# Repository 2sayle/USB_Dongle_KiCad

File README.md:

# USB Dongle (KiCad project)

KiCad project to create a custom USB-C key with mass storage and a microSD connector.
Find all the KiCad schematics and layout files.
Libraries containing custom footprints and symbols are available in ./Libraries folder.

## Hardware

- USB-C connector
- USB 2.0 High Speed Interface (through ULPI)
- STM32F730R8T microcontroller
- MicroSD connector
- Power LEDs
- GPIOs for SWD (Serial Wire Debug)

## Requirements

List any software requirements or dependencies needed to use or modify the project. For a KiCad project, this would include:

- KiCad EDA Suite version 7.0.2

## Installation

```
git clone https://github.com/2sayle/USB_Dongle_KiCad.git
```

## Usage

Explain how to use the project, with examples and screenshots if applicable.

## Documentation

Links to additional documentation for the project, such as a user manual or technical specifications.
- [STM32F730 Reference Manual](https://www.st.com/resource/en/reference_manual/rm0431-stm32f72xxx-and-stm32f73xxx-advanced-armbased-32bit-mcus-stmicroelectronics.pdf)
- [STM32F730R8 Datasheet](https://www.st.com/resource/en/datasheet/stm32f730i8.pdf)
- [ULPI Interface](http://ww1.microchip.com/downloads/en/DeviceDoc/334x.pdf)
- [USB ESD Protection](https://www.st.com/resource/en/datasheet/usbulc6-2m6.pdf)

Note: Datasheets are also available by selecting a component and pressing 'D' key, in KiCad schematics editor.

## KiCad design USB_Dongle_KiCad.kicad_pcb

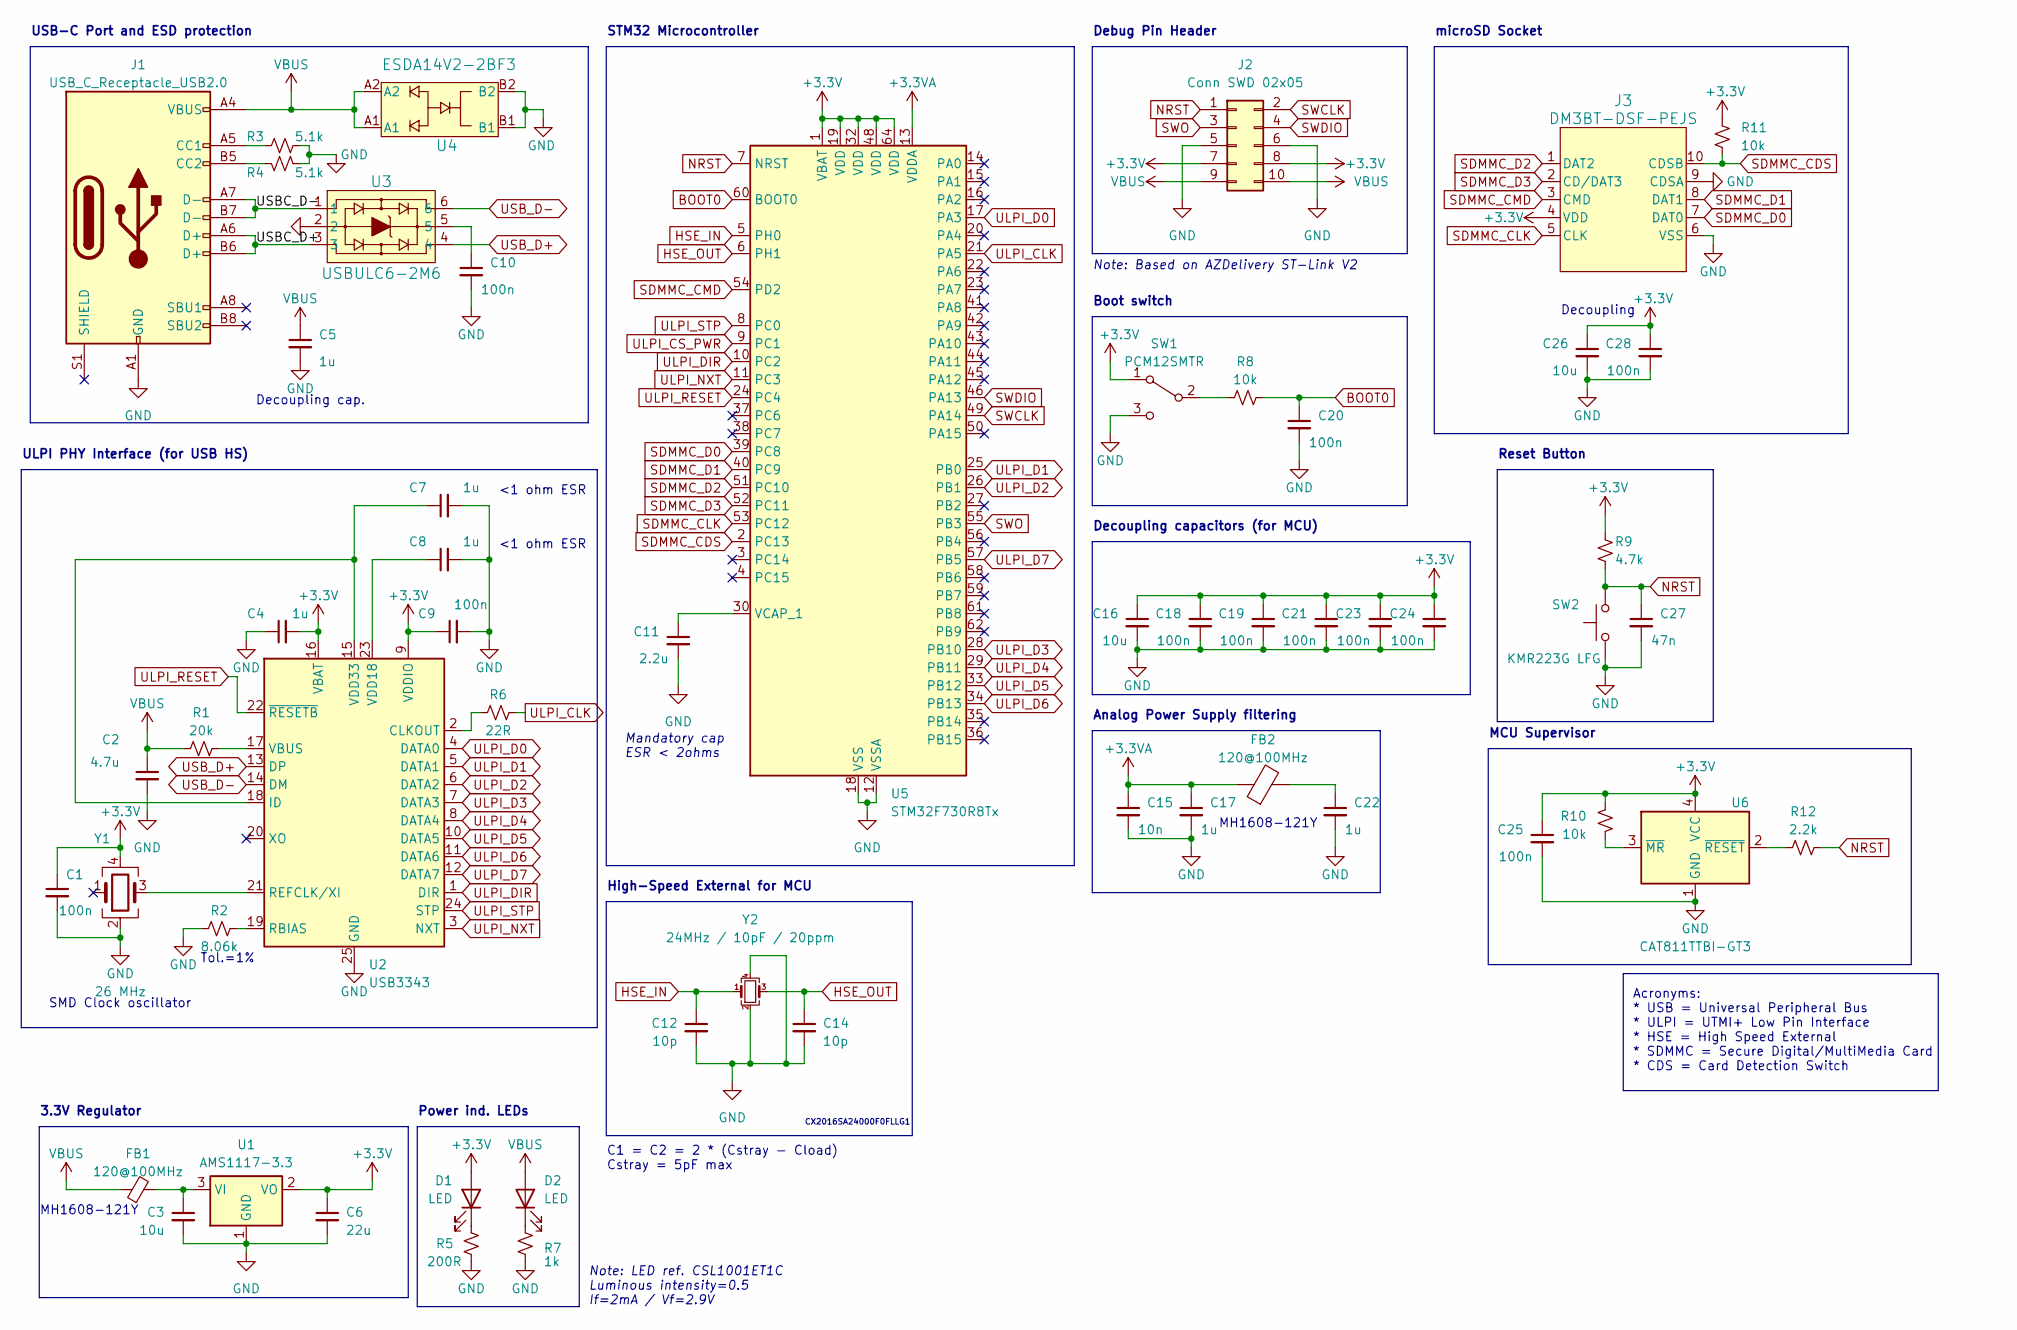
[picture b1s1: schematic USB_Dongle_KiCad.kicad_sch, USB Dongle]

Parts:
C1, C10, C18, C19, C20, C21, C23, C24, C25, C28: 100n; C_0603_1608Metric
C2: 4.7u; C_0805_2012Metric
C3, C16, C26: 10u; C_0805_2012Metric
C4, C5, C7, C8, C17, C22: 1u; C_0805_2012Metric
C6: 22u; C_0805_2012Metric
C9: 100n; C_0805_2012Metric
C11: 2.2u; C_0603_1608Metric
C12, C14: 10p; C_0603_1608Metric
C15: 10n; C_0603_1608Metric
C27: 47n; C_0603_1608Metric
D1, D2: LED; LED_0603_1608Metric
FB1, FB2: 120@100MHz; L_0603_1608Metric
J1: USB_C_Receptacle_USB2.0; USB_C_Receptacle_GCT_USB4105-xx-A_16P_TopMnt_Horizontal
J2: Conn SWD 02x05; PinHeader_2x05_P2.54mm_Vertical
J3: DM3BT-DSF-PEJS; DM3BT-DSF-PEJS_HIR
R1: 20k; R_0603_1608Metric
R2: 8.06k; R_0603_1608Metric
R3, R4: 5.1k; R_0603_1608Metric
R5: 200R; R_0603_1608Metric
R6: 22R; R_0603_1608Metric
R7: 1k; R_0603_1608Metric
R8, R10, R11: 10k; R_0603_1608Metric
R9: 4.7k; R_0603_1608Metric
R12: 2.2k; R_0603_1608Metric
SW1: PCM12SMTR; SW_SPDT_PCM12
SW2: KMR223G LFG; SW_Push_1P1T_NO_CK_KMR2
U1: AMS1117-3.3; SOT-223-3_TabPin2
U2: USB3343; QFN-24-1EP_4x4mm_P0.5mm_EP2.6x2.6mm
U3: USBULC6-2M6; MICROQFN6_1P45X1_STM
U4: ESDA14V2-2BF3; BGA_4V2-2BF3_STM
U5: STM32F730R8Tx; LQFP-64_10x10mm_P0.5mm
U6: CAT811TTBI-GT3; SOT-143
Y1: 26 MHz; Crystal_SMD_3225-4Pin_3.2x2.5mm
Y2: 24MHz / 10pF / 20ppm; Crystal_SMD_2016-4Pin_2.0x1.6mm

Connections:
+3.3V: C1.1, C4.2, C6.1, C9.1, C16.1, C18.1, C19.1, C21.1, C23.1, C24.1, C25.1, C26.1, C28.1, D1.2 (A), J2.7, J2.8, J3.4 (VDD), R9.1, R10.1, R11.2, SW1.1 (A), U1.2 (VO), U2.9 (VDDIO), U2.16 (VBAT), U5.1 (VBAT), U5.19 (VDD), U5.32 (VDD), U5.48 (VDD), U5.64 (VDD), U6.4 (VCC), Y1.4
+3.3VA: C15.1, C17.1, FB2.1, U5.13 (VDDA)
/USBC_D+: J1.A6 (D+), J1.B6 (D+), U3.3
/USBC_D-: J1.A7 (D-), J1.B7 (D-), U3.1
BOOT0: C20.1, R8.2, U5.60 (BOOT0)
GND: C1.2, C2.2, C3.2, C4.1, C5.2, C6.2, C7.2, C8.2, C9.2, C10.2, C11.2, C12.2, C14.2, C15.2, C16.2, C17.2, C18.2, C19.2, C20.2, C21.2, C22.2, C23.2, C24.2, C25.2, C26.2, C27.2, C28.2, J1.A1 (GND), J1.A12 (GND), J1.B1 (GND), J1.B12 (GND), J2.5, J2.6, J3.6 (VSS), J3.9 (CDSA), R2.1, R3.2, R4.2, R5.2, R7.2, SW1.3 (C), SW2.1, U1.1 (GND), U2.25 (GND), U3.2, U4.B1, U4.B2, U5.12 (VSSA), U5.18 (VSS), U5.31 (VSS), U5.47 (VSS), U5.63 (VSS), U6.1 (GND), Y1.2, Y2.2, Y2.4
HSE_IN: C12.1, U5.5 (PH0), Y2.1
HSE_OUT: C14.1, U5.6 (PH1), Y2.3
NRST: C27.1, J2.1, R9.2, R12.2, SW2.2, U5.7 (NRST)
unnamed: C10.1, U3.5
unnamed: C22.1, FB2.2
unnamed: D1.1 (K), R5.1
unnamed: D2.1 (K), R7.1
unnamed: J1.A5 (CC1), R3.1
unnamed: J1.B5 (CC2), R4.1
unnamed: R8.1, SW1.2 (B)
unnamed: C3.1, FB1.2, U1.3 (VI)
unnamed: R6.1, U2.2 (CLKOUT)
unnamed: C7.1, U2.15 (VDD33), U2.18 (ID)
unnamed: R2.2, U2.19 (RBIAS)
unnamed: U2.21 (REFCLK/XI), Y1.3
unnamed: R1.2, U2.17 (VBUS)
unnamed: C8.1, U2.23 (VDD18)
unnamed: C11.1, U5.30 (VCAP_1)
unnamed: R10.2, U6.3 (~MR)
unnamed: R12.1, U6.2 (~RESET)
SDMMC_CDS: J3.10 (CDSB), R11.1, U5.2 (PC13)
SDMMC_CLK: J3.5 (CLK), U5.53 (PC12)
SDMMC_CMD: J3.3 (CMD), U5.54 (PD2)
SDMMC_D0: J3.7 (DAT0), U5.39 (PC8)
SDMMC_D1: J3.8 (DAT1), U5.40 (PC9)
SDMMC_D2: J3.1 (DAT2), U5.51 (PC10)
SDMMC_D3: J3.2 (CD/DAT3), U5.52 (PC11)
SWCLK: J2.2, U5.49 (PA14)
SWDIO: J2.4, U5.46 (PA13)
SWO: J2.3, U5.55 (PB3)
ULPI_CLK: R6.2, U5.21 (PA5)
ULPI_CS_PWR: U5.9 (PC1)
ULPI_D0: U2.4 (DATA0), U5.17 (PA3)
ULPI_D1: U2.5 (DATA1), U5.25 (PB0)
ULPI_D2: U2.6 (DATA2), U5.26 (PB1)
ULPI_D3: U2.7 (DATA3), U5.28 (PB10)
ULPI_D4: U2.8 (DATA4), U5.29 (PB11)
ULPI_D5: U2.10 (DATA5), U5.33 (PB12)
ULPI_D6: U2.11 (DATA6), U5.34 (PB13)
ULPI_D7: U2.12 (DATA7), U5.57 (PB5)
ULPI_DIR: U2.1 (DIR), U5.10 (PC2)
ULPI_NXT: U2.3 (NXT), U5.11 (PC3)
ULPI_RESET: U2.22 (~RESETB), U5.24 (PC4)
ULPI_STP: U2.24 (STP), U5.8 (PC0)
USB_D+: U2.13 (DP), U3.4
USB_D-: U2.14 (DM), U3.6
VBUS: C2.1, C5.1, D2.2 (A), FB1.1, J1.A4 (VBUS), J1.A9 (VBUS), J1.B4 (VBUS), J1.B9 (VBUS), J2.9, J2.10, R1.1, U4.A1, U4.A2

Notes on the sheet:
Decoupling
USB-C Port and ESD protection
Reset Button
Decoupling capacitors (for MCU)
Note: LED ref. CSL1001ET1C Luminous intensity=0.5 If=2mA / Vf=2.9V
Tol.=1%
MH1608-121Y
Decoupling cap.
MCU Supervisor
3.3V Regulator
Analog Power Supply filtering
<1 ohm ESR
High-Speed External for MCU
Note: Based on AZDelivery ST-Link V2
Mandatory cap ESR < 2ohms
CX2016SA24000F0FLLG1
SMD Clock oscillator
microSD Socket
C1 = C2 = 2 * (Cstray - Cload) Cstray = 5pF max
Debug Pin Header
Power ind. LEDs
ULPI PHY Interface (for USB HS)
STM32 Microcontroller
Acronyms: * USB = Universal Peripheral Bus * ULPI = UTMI+ Low Pin Interface * HSE = High Speed External * SDMMC = Secure Digital/MultiMedia Card * CDS = Card Detection Switch
Boot switch

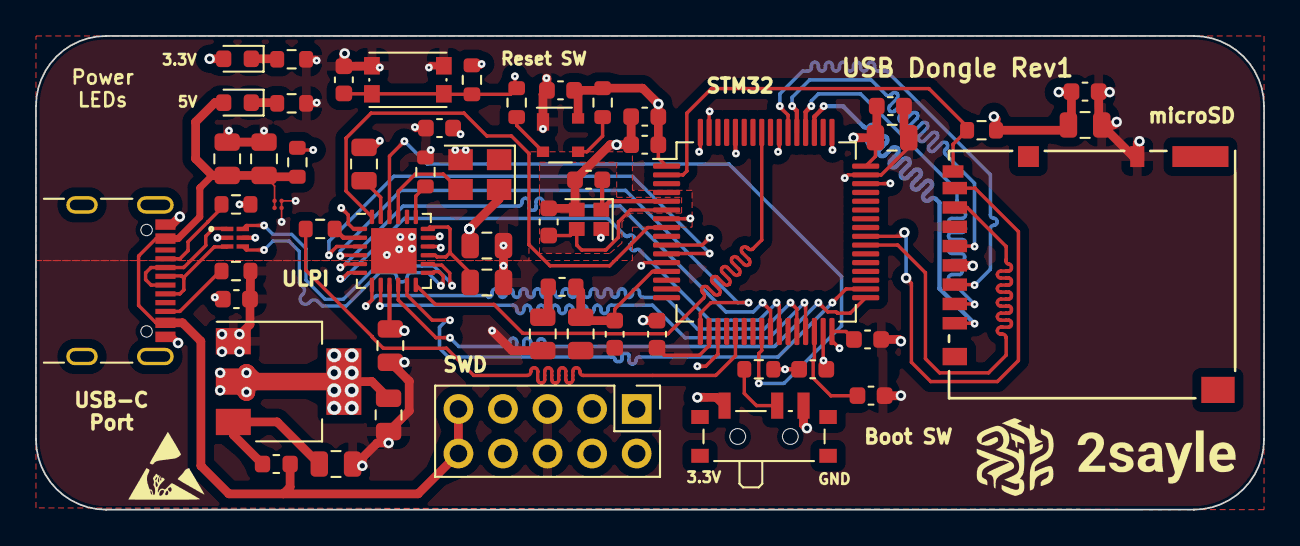
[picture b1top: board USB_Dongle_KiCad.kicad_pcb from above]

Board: 6 copper layers, 70.0 x 27.0 mm, 56 parts (0 on the bottom side), 52 nets.

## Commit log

2024-05-02 Added project files
2024-05-02 Tiny updates in the schematics
2024-05-02 Updated gitignore file
2024-05-02 Removed unnecessary documents
2024-05-02 Added: New microSD component
2024-05-03 Added: Clock oscillator for ULPI
2024-05-03 Added: Pull-down resistors for CCx pins (USB-C port)
2024-05-03 Executed DRC and ignored irrelevant warnings
2024-05-03 Assigned footprints to symbols
2024-05-03 Created layout
2024-05-04 Updated: PCB design rules
2024-05-04 Update: Routing of high speed tracks
2024-05-05 Update: near end of layout
2024-05-05 Added: 3D models for some components
2024-05-05 Various fixes and other 3D models added
2024-05-15 Update: New routing after ULPI component change
2024-05-17 Improved layout
2024-05-18 Added: 3D screenshot
2024-06-29 Small changes
2026-02-03 Fix: Value of external capacitor for VCAP1
2026-03-28 Add PCB view image to README
    Added a PCB view image to the README.
